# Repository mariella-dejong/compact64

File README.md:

# Compact 64

A smaller form-factor Commodore 64 that is built around the **original MOS
6510 CPU, VIC-II and SID chips**.

The project starts from a faithful KiCad replica of the C64 "250407"
motherboard and evolves it step by step: the original chips stay, while the
rest of the board is either kept as-is or replaced with present-day parts and
modern solutions where that makes the machine smaller, easier to build or more
convenient to use.

> **Status:** work in progress. The schematic is being redesigned step by
> step, starting from the 250407 replica. The PCB layout is not kept in sync
> with these changes and reflects an earlier state of the design: the board
> will be laid out again from scratch for the smaller form factor once the
> schematic is complete. Do not use the current PCB files for manufacturing.
> Nothing here has been built or tested yet in its modified form.

## Goals

- Keep the heart of the C64 genuine: the original 6510, VIC-II and SID chips
  run the show.
- Shrink the board to a smaller form factor.
- Make it buildable today: use parts that can actually be sourced, and put
  chips that can only be salvaged from old machines in sockets.
- Replace parts of the design that are obsolete, hard to source or
  inconvenient with modern equivalents.
- Stay open: publish all design files in their native, editable format.

## Roadmap

The work is tracked in the issue tracker. In broad strokes:

**Phase 1 - Hardware: a clean, modern base design**

- Import the reverse-engineered 250407 design (#1)
- Upgrade the design to KiCad 10 (#2)
- Restructure the hierarchical schematic (#3)
- Make schematic and PCB fully consistent (clean ERC and DRC) (#4)
- Add LCSC part numbers for sourceable components, NTSC variants first (#5)
- Use IC sockets for chips that can no longer be sourced new (#6)
- Replace obsolete passive and other non-chip components (#14, #15)

**Phase 2 - Hardware: modernisation**

- Replace the RF modulator with an on-board composite and S-Video circuit
  (#8), and add S-Video and audio outputs (#24, #9)
- Power the board from a single 12 V DC input (#10) and generate the supply
  rails from it (#26), starting with the 5 V buck converter (#28),
  `CAN+5V` (#34), `+12V` (#36, replaced by `+9V` in #73), the cassette
  motor supply (#41) and `+3V3` (#44), and remove the 9 V AC input (#37)
- Add a supervisor microcontroller that only lets the system power up when
  it is safe to do so (#46)
- Replace RAM and ROM with a microcontroller-based solution (#11)
- Replace CIA1 (#25) and CIA2 (#68) with a microcontroller-based solution
- Replace the keyboard connector with a USB keyboard to keyboard-matrix
  bridge (#12); the USB keyboard port is on the CIA1 controller (#25)
- Move to the chip set of the later C64 boards: the 8580 SID (#73), the 8562
  VIC-II (#74), later the PAL 8565 (#152), and the 8500 CPU (#75)

**Phase 3 - Firmware and software**

- Wireless (Bluetooth or Wi-Fi) media access, for example an emulated disk
  drive fed by a PC application (#13)
- Firmware for the microcontroller-based subsystems above

## Repository layout

| Path                  | Contents                                                        |
| --------------------- | --------------------------------------------------------------- |
| `hardware/main-board` | KiCad project of the main board (starts as the 250407 replica)  |
| `hardware/components` | KiCad symbols and footprints that KiCad's own libraries lack    |
| `hardware/led-module` | KiCad project of the status LED module, cabled to the main board |
| `LICENSES/`           | Full texts of all licences used in this repository              |
| `LICENSE.md`          | Which licence applies to which part of the repository           |
| `NOTICE.md`           | Credits, third-party attributions and trademark notices         |
| `CONTRIBUTING.md`     | How to contribute, and the conventions for issues and pull requests |

Firmware and software will get their own top-level directories once that work
starts.

## Tools

The hardware is designed in [KiCad](https://www.kicad.org/) 10 (#2). The
imported replica was last saved with KiCad 9.0.

## Contributing

Contributions are welcome. See [CONTRIBUTING.md](CONTRIBUTING.md) for how to
get started, the conventions for issues and pull requests, and the licensing
of contributions.

## Credits

This project would not exist without the C64 250407 replica by **Bwack** and
the people who helped create it, most notably **Michael K. (Der Alte
Bastler)**, who started the reverse engineering effort. See
[NOTICE.md](NOTICE.md) for the full list of credits and third-party
attributions.

The composite and S-Video output circuit that replaces the RF modulator is
derived from the C64 RF Modulator Replacement by **mbarszcz-pcb**.

- Upstream project: <https://github.com/bwack/C64-250407-Replica-KiCad>
- RF modulator replacement: <https://github.com/mbarszcz-pcb/c64-rf-modulator-replacement>

## Licence

In short:

- **Hardware** design files (`hardware/`) are licensed under the
  [CERN Open Hardware Licence Version 2 - Strongly Reciprocal](LICENSES/CERN-OHL-S-2.0.txt)
  (CERN-OHL-S-2.0).
- **Firmware and software** will be licensed under the
  [Apache License 2.0](LICENSES/Apache-2.0.txt).
- **Documentation** outside `hardware/` is licensed under
  [Creative Commons Attribution 4.0 International](LICENSES/CC-BY-4.0.txt)
  (CC-BY-4.0).

See [LICENSE.md](LICENSE.md) for the details, including how to attribute this
work when you reuse it.

## Disclaimer

This is an independent hobby project. It is not affiliated with, endorsed by
or sponsored by the owners of the Commodore, Commodore 64 or C64 trademarks,
or by MOS Technology or its successors. See [NOTICE.md](NOTICE.md).

The design files are provided as-is, without any warranty. Building
electronics involves risks, including working with mains-powered equipment
and soldering; you build and use anything from this repository at your own
risk.

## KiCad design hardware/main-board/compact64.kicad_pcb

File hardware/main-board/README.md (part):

# Main board

KiCad project of the Compact 64 main board. Open `compact64.kicad_pro` in KiCad.

The design starts as an unmodified copy of the
[C64 250407 Replica](https://github.com/bwack/C64-250407-Replica-KiCad) by
Bwack: a reverse-engineered replica of the Commodore 64 assembly 250407
motherboard (PCB KU-14194HB). It will be modified step by step into the
Compact 64 main board; see the [project README](../../README.md) for the
roadmap.

## Status

The schematic is under active redesign. The PCB layout is not updated along
with it: it includes the changes up to and including the HF module
replacement (#8), but not the `Power Supply` sheet (#10) or later changes.
Because the board will be laid out again from scratch for the smaller form
factor once the schematic is complete, intermediate schematic changes are
not carried over to the current layout. Expect the DRC schematic parity
check to report these differences, and do not use the current PCB files for
manufacturing.

The board now runs from a single 12 V DC input (#10, #26). All supply rails
are made from it on the `Power Supply` sheet. The original power brick input
is gone (#37): the power connector CN7, the 9 V AC and `+9V_UNREG`, and the
power switch SW1, so the board has no power switch.

The SID is now an 8580 on a 9 V supply (#73), and the VIC-II an HMOS-II part
on 5 V (#74), so the board no longer needs 12 V anywhere and the `+12V` rail
is gone. The VIC-II is the PAL 8565 (#152), because the NTSC 8562 can hardly
be bought any more; an 8562 still works with the NTSC clock setting.

The VIC-II's colour and dot clocks now come from a clock synthesizer on the
`System Clocks` sheet (#76). It replaces the PLL of the original board, whose
MC4044 can no longer be bought, and the colour clock divider that
synchronized the buck converters.

What is left of the original 250407 circuit, the 6510 with the cassette
port and the expansion port, is now on one flat sheet, `CPU, Cassette and Expansion Port` (#84, #107), with SMD passives and
reference numbers in the 200 range, see
[CPU, cassette and expansion port](#cpu-cassette-and-expansion-port). Its
power-on reset timer is gone: the supervisor now resets the system at
start-up (#89), see [Soft reset](#soft-reset).

The PLA (U17), the 74LS139 (U15), the 7408 (U27) and the `~AEC` inverter of
the original board are replaced by a CPLD on the `PLA Replacement` sheet
(#83), see [PLA replacement](#pla-replacement).

The supervisor has a micro SD card slot (#95), from which it will load disk
and tape images (#13), see [SD card slot](#sd-card-slot).

The status LEDs (power, ready, activity, error) sit on a separate LED module
that connects to the supervisor with a short cable, so that they can be
mounted in the case (#54), see [Status LEDs](#status-leds). The original
power LED connector is gone.

## Compatibility

These changes make the Compact 64 behave differently from an original C64.
Check them before using software or hardware that depends on them.

### CIA time-of-day clocks run from a crystal

- **Original C64:** both CIAs (U1 and U2) get a 50 Hz or 60 Hz signal on
  their TOD input (pin 19). It is derived from the 9 V AC of the power brick
  and buffered by gate A of U27, so the clocks follow the mains frequency.
- **Compact 64:** there is no 9 V AC (#37). Both CIAs are replaced by
  microcontrollers (#25, #68) that make the 50 Hz or 60 Hz reference from
  their own crystal, as selected by bit 7 of CRA (see
  [CIA 1, keyboard and joysticks](#cia-1-keyboard-and-joysticks) and
  [CIA 2, serial port and user port](#cia-2-serial-port-and-user-port)).
  U27 is gone as well (#83).
- **Not affected:** software that uses the time-of-day clocks, the TOD
  alarms or the CIA timers, provided the firmware implements them.
- **Affected:** only software that expects the TOD clocks to follow the
  mains frequency exactly. The crystal reference is more stable than the
  mains, so a TOD clock can drift a little differently from an original C64.

### User port pins 10 and 11 carry no 9 V AC

- **Original C64:** pins 10 and 11 of the user port (CN2) carry the 9 V AC of
  the power brick, one side through fuse F1.
- **Compact 64:** both pins are unconnected, and not grounded (#37). The user
  port is now J1602 on the `CIA2, Serial Port and User Port` sheet (#68).
- **Affected:** devices that take their power from these pins, such as some
  RS-232 interfaces and EPROM programmers. They need their own supply.
  Devices that only use the +5 V on pin 2 and the data lines are not
  affected.

### No 8-pin DIN A/V connector

- **Original C64:** the A/V connector (CN5) is an 8-pin DIN socket with luma
  (pin 1), ground (pin 2), audio out (pin 3), composite video (pin 4), audio
  in (pin 5) and chroma (pin 6).
- **Compact 64:** CN5 is removed (#24). The same signals are on a 4-pin
  mini-DIN S-Video socket (J501) and three RCA jacks (J502), see
  [Audio and video connectors](#audio-and-video-connectors).
- **Affected:** C64 A/V cables with a DIN plug, such as DIN to RCA, DIN to
  S-Video and DIN to SCART cables. Use standard S-Video and RCA cables
  instead.

### RAM and ROM are served by a microcontroller

- **Original C64:** eight 4164 DRAMs, the BASIC, KERNAL and character ROMs,
  and a 2114 colour RAM.
- **Compact 64:** a microcontroller (U1401) serves all of them from its own
  memory (#11), see [RAM and ROM replacement](#ram-and-rom-replacement). It
  loads the ROM images from an EEPROM. The ROM images are not part of this
  project.
- **Affected:**
  - The board does not start without the controller's firmware and ROM
    images.
  - ROM upgrades that replace a chip, such as a replacement KERNAL chip,
    cannot be fitted. Write a different image to the EEPROM instead.
  - The RAM contents at power-up are set by the firmware, not by the DRAMs'
    power-up pattern. The same goes for other details of DRAM behaviour,
    such as what ends up in RAM when the 6510 writes to $00 or $01.
- **Not affected:** bank switching, cartridges and the VIC-II bank
  selection. The CPLD that replaces the PLA (U301) decodes them as before.

### CIA 1 is emulated by a microcontroller, and the keyboard is USB

- **Original C64:** a 6526 CIA (U1) at $DC00 scans the keyboard matrix on
  connector CN1 and reads the two control ports (CN8, CN9).
- **Compact 64:** a microcontroller (U1501) takes the place of CIA 1 (#25),
  see [CIA 1, keyboard and joysticks](#cia-1-keyboard-and-joysticks). The
  keyboard is a USB keyboard on a USB-A socket (J1501), and the firmware
  presents it to the 6510 as the C64 keyboard matrix. RESTORE is a key on
  the USB keyboard chosen by the firmware. The control ports are new DE-9
  sockets (J1502, J1503) with the original pinout.
- **Affected:**
  - The board does not start without the controller's firmware.
  - An original C64 keyboard, or anything else made for the 20-pin keyboard
    connector, cannot be connected.
  - How closely the 6526 is matched (timers, interrupts, the serial shift
    register, keyboard ghosting) depends on the firmware. Programs that rely
    on exact CIA timing or on unusual keyboard matrix tricks need firmware
    that reproduces them.
  - The digital control port lines now have 10k pull-ups to +5V and a
    100 Ohm series resistor, instead of the 6526's internal pull-ups. The
    levels stay the same: a line idles at 5 V and a pressed switch pulls it
    to about 0.05 V.
- **Not affected:** paddles and the POT lines (the 4066 that switches them,
  now U1702, works as before), the light
  pen input of the VIC-II, cassette read and the serial bus SRQ on `~FLAG`,
  and `CNT` and `SP` on the user port.

### CIA 2 is emulated by a microcontroller

- **Original C64:** a 6526 CIA (U2) at $DD00 selects the VIC-II bank, drives
  and reads the serial bus through U8 (7406), and serves the user port
  (CN2).
- **Compact 64:** a microcontroller (U1601) takes the place of CIA 2 (#68), see
  [CIA 2, serial port and user port](#cia-2-serial-port-and-user-port). The
  serial port (J1601) and the user port (J1602) keep their original pinout.
- **Affected:**
  - The board does not start without the controller's firmware.
  - How closely the 6526 is matched (timers, NMI timing, the serial shift
    register, `~PC` and `~FLAG`) depends on the firmware. Fast loaders,
    RS-232 on the user port and demos that switch the VIC-II bank at exact
    cycles need firmware that reproduces the 6526 cycle by cycle.
  - The serial bus driver U1602 (SN74LVC06A) sinks up to 24 mA, the original
    7406 up to 40 mA. Every device on the bus adds its own pull-up of about
    1k (5 mA). The C64 and three such devices stay within the rating; more
    devices with 1k pull-ups may pull the low level up too far.
  - The user port lines have 4.7k pull-ups to +5V, a 100 Ohm series
    resistor and a TVS diode instead of the 6526's internal pull-ups. A line
    still idles at 5 V. An output that is set high is released to the
    pull-up instead of being driven, so its rising edge is a little slower
    (about 0.5 us with 100 pF of cable).
- **Not affected:** the VIC-II bank selection after reset (bank 0, also
  before the firmware runs), the serial bus pinout, the user port pinout
  except pins 10 and 11 (see above), and `CNT` and `SP` of CIA 1 on the user
  port.

### The CPU is an 8500

- **Original C64:** the 250407 board has an NMOS 6510 CPU (U7).
- **Compact 64:** the CPU socket (U201) takes the HMOS-II 8500 of the later
  C64C boards (#75), see
  [CPU, cassette and expansion port](#cpu-cassette-and-expansion-port). The
  8500 is the 6510 made in the newer process: same pinout, same 5 V supply,
  same bus timing and the same processor port, so the circuit is the same
  for both. It also runs cooler. A 6510 works in the socket as well. This
  README calls the CPU the 6510 when it describes its pins and bus cycles.
- **Affected:**
  - The unused bits 6 and 7 of the processor port ($01) keep a written value
    for a while after the port is switched to input, until the charge leaks
    away. This takes noticeably longer on an 8500 than on a 6510 (VICE
    assumes about 1.5 s against about 0.35 s), and on both chips it depends
    strongly on the chip and the temperature. A few copy protections and
    test programs measure it.
  - The unstable undocumented opcodes (such as ANE/XAA and LXA) use a
    "magic constant" that differs between chips, including between 6510 and
    8500 chips, and with temperature. Programs that rely on them may behave
    differently, as they also do between two original C64s.
  - Original 8500 and 6510 chips are only available second-hand.
- **Not affected:** the documented instruction set, the bus and interrupt
  timing, the processor port bits 0 to 5 (memory configuration and the
  cassette lines) and their pull-ups.
- **Not the 8502:** the 8502 is the C128's CPU and is not a drop-in
  replacement.

### The SID is an 8580

- **Original C64:** the 250407 board has a 6581 SID (U18) with 12 V on VDD
  and 470 pF filter capacitors.
- **Compact 64:** the SID socket (U1701) takes the 8580 of the later C64
  boards, with 9 V on VDD and 22 nF filter capacitors (#73), see
  [SID and audio output](#sid-and-audio-output).
- **Affected:**
  - Music sounds different. The 8580's filter is cleaner and more linear,
    it has less background noise and its combined waveforms differ. Music
    written for the 6581, which is most classic SID music, can sound
    noticeably different, especially where it uses the filter.
  - Samples played by writing the volume register ($D418) are almost silent
    on an 8580. A resistor from EXT IN to ground can bring them back; the
    board does not have one.
  - A 6581 must not be fitted: it would get 9 V instead of 12 V on VDD and
    the wrong filter capacitors.
- **Not affected:** the SID's registers, the paddles and the audio
  connectors. Modern SID replacements usually accept 9 V on VDD; check the
  specific product.

### The VIC-II is a PAL 8565

- **Original C64:** the 250407 board has an NMOS 6567 VIC-II (U19, NTSC) with
  12 V on VDD (pin 13) and a 470 Ohm luma pull-up; PAL boards have the 6569.
- **Compact 64:** the VIC-II socket (U504) takes the HMOS-II 8565 of the later
  PAL C64 boards (#152), with 5 V on pin 13 and a 1 kOhm luma pull-up (#74),
  see [VIC-II](#vic-ii). The NTSC 8562 has the same pinout and supply and
  also works, with the NTSC clock setting in the supervisor firmware; the
  board was built around it first, but it can hardly be bought any more.
- **Affected:**
  - The video timing is PAL: 63 cycles per line and 312 lines (50 Hz), with
    the CPU at 0.985 MHz, the same as a PAL C64 with a 6569 or 8565.
    Software written for PAL machines runs as on a PAL C64; NTSC-only
    software that depends on 65 cycles and 263 lines may not.
  - The SID runs from the PAL `PHI2`, so music plays at the pitch of a PAL
    C64.
  - Colours and luma levels differ slightly from the NMOS 6567 and 6569.
  - The 8565 shows "grey dots" when some colour registers are written at
    certain cycles, which a few demos trigger.
  - A 6567 or 6569 does not work in this socket: they need 12 V on pin 13.
- **Not affected:** the registers, sprites, raster interrupts and the light
  pen.

### The video clocks come from a clock synthesizer

- **Original C64:** a PLL on the 250407 board (Y1, U29 to U32) makes the
  colour clock from a 14.31818 MHz crystal and locks the dot clock to it.
  PAL or NTSC is set with the crystal, some component values and a jumper.
- **Compact 64:** an MS5351M clock synthesizer (Y1202) makes both clocks from
  one PLL and a 25 MHz crystal (#76), see [System clocks](#system-clocks).
  The supervisor programs it over I2C, so PAL or NTSC becomes a firmware
  setting. PAL is the default, for the 8565 (#152); NTSC is only for a board
  with an 8562. The setting must match the fitted VIC-II.
- **Affected:**
  - Without supervisor firmware the VIC-II gets no clocks. The board already
    needs firmware for RAM, ROM and both CIAs.
- **Not affected:** the video timing and the ratio between the dot clock
  and the colour clock (4/9 on PAL, 4/7 on NTSC), which the synthesizer makes
  exactly. The colour
  carrier is as accurate as the 25 MHz crystal (10 ppm).

### The PLA is a CPLD

- **Original C64:** a 906114-01 PLA (U17) decodes the memory map, a 74LS139
  (U15) the I/O area, and a 7408 (U27) and a 7406 gate (U8) make `RDY`,
  `CAEC`, `~COLORAM` and `~AEC`.
- **Compact 64:** one XC9572XL CPLD (U301) does all of this (#83), with logic
  written from the PLA's documented equations (#93), see
  [PLA replacement](#pla-replacement). The supervisor checks its design at
  start-up and programs it when needed (#86).
- **Affected:**
  - The board does not start without the supervisor firmware, which also
    enables the CPLD's outputs.
  - The chip selects come out about 10 ns after the inputs change, earlier
    than from the PLA and the 74LS139. Cartridges that are sensitive to PLA
    timing need testing on the prototype.
  - The chip selects on the expansion port (`~ROML`, `~ROMH`, `~I/O1`,
    `~I/O2`) are 3.3 V signals, at TTL levels like the original ones.
- **Not affected:** the memory map, bank switching through $01, the
  cartridge modes set by `~GAME` and `~EXROM` (including Ultimax), the I/O
  map and DMA through `~DMA`, provided the logic matches the PLA (#93).

## Power supply

The board is being converted to a single 12 V DC input (#10, #26). The rails
made from it so far are on the `Power Supply` sheet:

| Rail       | Made by                                                     | Rated for | Issue |
| ---------- | ----------------------------------------------------------- | --------- | ----- |
| `12V_PROT` | Input stage: barrel jack, polyfuse, reverse polarity and TVS protection | 2.5 A (polyfuse hold current) | #10   |
| `12V_MAIN` | Power switch (Q606, Q607), set by the power switch on the case; feeds `+3V3` and the input switch | 2.5 A | #109 |
| `12V_IN_SW` | Input switch (Q604, Q605), turned on by the supervisor; feeds every rail below except `+3V3` | 2.5 A | #47   |
| `+5V`      | LM61440 synchronous buck converter (U701), synchronized to the clock synthesizer | 2 A       | #28   |
| `CAN+5V`   | L78M05 linear regulator (U801) behind four M7 diodes        | 500 mA    | #34   |
| `+9V`      | CJ78M09 linear regulator (U902) from the switched 12 V input | 500 mA (regulator) | #36, #73 |
| `CASS_POWER` | TPS562208 synchronous buck converter (U1101), switched on and off by the 6510 | 2 A       | #41   |
| `+3V3`     | LM61440 synchronous buck converter (U1001), synchronized to the clock synthesizer; backed up from `+5V` by U1002 (#110) | 1 A budget (converter rated 4 A) | #44, #110 |

The HF module replacement (U501, a 78L05 behind R501) also runs from the
switched 12 V input: the `Power Supply` sheet passes `12V_IN_SW` on through a
sheet pin of the same name to the `VIC-II, HF Module Replacement and AV out`
sheet. The `5V Buck` sheet's output reaches the root sheet through the `5V_OUT` sheet
pin, where it connects to the `+5V` power symbol.

The `System Clocks` sheet supplies the sync clock for the switching parts,
see [System clocks](#system-clocks). U1201 (74AHCT1G08) passes output CLK2
of the clock synthesizer, about 445 kHz, only once `PGOOD` is high. It
reaches the 5 V and 3.3 V buck converters through the `SYNC_CLK_IN` sheet pin
of the `Power Supply` sheet. CLK2 comes from the same PLL as the colour and
dot clocks, so the converters' interference has a fixed relation to the
video timing. U1201 runs from `CAN+5V`.

`PGOOD` combines the open-drain PGOOD outputs of both buck converters (U701
and U1001) with the pull-ups R706 and R1003 (200k each) on `CAN+5V`: a
wired-AND. It leaves the `Power Supply` sheet through the `PGOOD` sheet pin.
It goes high once both outputs are in regulation, after the 1.5 ms to 2.5 ms
PGOOD delay. The supervisor reads it on GPIO3 through R1330 (#49), see [Chip
and rail checks](#chip-and-rail-checks). If either rail drops out of
regulation, the sync clock stops and both converters run unsynchronized at
about 400 kHz, set by R701 and R1002, until `PGOOD` returns.

### 12 V path

The 12 V input passes three stages, and each stage has its own net name:

```
J601 ── F601 ── Q601/Q602 ── 12V_PROT ── Q606/Q607 ── 12V_MAIN ── Q604/Q605 ── 12V_IN_SW
 jack   fuse    reverse         TVS D602   power switch   U1001 (+3V3)  input switch  all other rails
                polarity        C605       (case switch)                (supervisor)
```

| Net | Connected |
| --- | --------- |
| `12V_PROT` | After the reverse polarity protection: TVS D602, C605 (220 nF), the zener D601 of Q601/Q602, the power switch Q606/Q607 with R606 and C604 |
| `12V_MAIN` | After the power switch: C601, C602, 3V3 buck converter U1001 with its input capacitors and EN pull-up R1001, the input switch Q604/Q605 with R605 and C603 |
| `12V_IN_SW` | After the input switch: 5V buck converter U701 with R705, cassette buck converter U1101 with R1103, `CAN+5V` (D801 to U801), `+9V` (FB901 to U902), HF module replacement (R501) |

The converter sheets call their input `VIN`. That hierarchical label always
means "the input of this converter" and connects to `12V_MAIN` or
`12V_IN_SW` on the `Power Supply` sheet.

### Power switch

The power switch (#109) turns the whole board on and off, including
`+3V3` and the supervisor. A small switch in the case (on J602) steers a
P-channel MOSFET pair, so the switch itself only carries microamps.

```
12V_PROT ──┬───────────── Q606/Q607 (2x AO3401A, source on 12V_PROT) ── 12V_MAIN
           │                   │ gate (PWR_SW_GATE)
           ├── R606 100k ──────┤
           └── C604 47 nF ─────┤
                               └── R607 100k ── J602 pin 2 ── case switch ── J602 pin 1 ── GND
```

- **Off (switch open):** R606 holds the gate at the source, so Q606 and
  Q607 are off. They are mounted the other way round from Q601/Q602
  (source on the input side), so their body diodes block, and the board
  draws nothing.
- **On (switch closed):** R606 and R607 divide the gate to about half the
  input voltage: about -6 V gate-source at 12 V, and about -10.75 V at the
  21.5 V clamping voltage of D602, within the AO3401A's +/-12 V limit. Two
  in parallel carry the full 2.5 A at about 0.17 W, like the input switch.
- **Why a second pair:** Q601/Q602 (reverse polarity protection) cannot be
  reused. Their body diodes conduct in the normal direction, so the board
  would keep running through them while they are off.
- **C604 (47 nF):** slows the switch-on (time constant about 2.4 ms), so
  that C601, C602 and the converters' input capacitors charge gently, and
  keeps the gate at the source when the adapter is plugged in with the
  switch off.
- **ESD:** the switch sits in the case on a cable. R607 is on the gate side
  of J602, so a discharge into the cable reaches the gate only through
  100k, where C604 absorbs it. D602 and C605 sit before the switch, so the
  input stays protected while it is off.
- **Power-off order:** switching off looks exactly like unplugging the
  adapter. `+3V3` is backed up from `+5V` (#110), so it never drops while
  `+5V` is still up, see [Backup from `+5V`](#backup-from-5v-110).
- **Consequences:** with the switch off, the supervisor is off too, so the
  SD card cannot be reached over USB, and a firmware update cannot delay
  the switch-off; the firmware tolerates a sudden power loss (#111).
- **Reverse polarity:** Q601/Q602 still block a reversed input, and Q606
  and Q607 stay off.

| Ref | Part | LCSC | Package |
| --- | ---- | ---- | ------- |
| Q606, Q607 | AO3401A | C15127 | SOT-23 |
| R606, R607 | 100k | C25741 | 0402 |
| C604 | 47 nF | C1622 | 0603 |
| C605 | 220 nF | C21120 | 0603 |
| J602 | 1x2 pin header, 2.54 mm, for the case switch | C32713268 | THT |

The case switch itself is not on the board. Any small latching switch
works, for example a KCD11 mini rocker switch that snaps into a 10 x 15 mm
cut-out.

### Input switch

The supervisor (U1301) decides when the system may start (#47). It does this
with one switch in the 12 V input: every rail except `+3V3` runs from the
switched input `12V_IN_SW`, so a single signal turns them all on or off.
`+3V3` stays on `12V_MAIN`, before the input switch, because it powers the
supervisor.

**Circuit:**

- Q604 and Q605 (AO3401A, P-channel) in parallel, sources on `12V_MAIN`,
  drains on `12V_IN_SW`. Two in parallel halve the on-resistance to about
  28 mOhm, so they dissipate about 0.17 W at 2.5 A.
- R605 (100k) pulls their gates to the source, so they are off by default.
- Q603 (AO3400A, N-channel) pulls the gates down through R604 (100k). R604
  and R605 form a divider, so the gates go to about half the input voltage
  instead of to ground: about -6 V gate-source at 12 V, and about -10.75 V
  at the 21.5 V clamping voltage of D602, within the AO3401A's +/-12 V
  limit.
- Q603's gate is driven by `POWER_ON` through R602 (10k), with R603 (200k)
  to ground.
- C603 (47 nF) between the gates and `12V_MAIN` does two things. It keeps
  the gates at the source voltage when the adapter is plugged in, so the
  MOSFETs' gate-drain capacitance cannot turn them on briefly. And it slows
  down switching: the gates move with a time constant of about 2.4 ms when
  turning on and about 4.8 ms when turning off, which limits the inrush
  current into the input capacitors of the rails to well under 1 A.
- A PWR_FLAG on `12V_IN_SW` tells ERC that the MOSFETs drive this net.

**Operation** (12 V input):

| State | `POWER_ON` | Q603 gate | Q604/Q605 gate | Q604/Q605 gate-source | `12V_IN_SW` |
| ----- | ---------- | --------- | -------------- | --------------------- | ----------- |
| Off   | 0 V or not driven | 0 V | 12 V | 0 V | off |
| On    | 3.3 V      | 3.14 V    | 6 V            | -6 V                  | about 12 V  |

Q603 is fully on at 3.14 V (threshold at most 1.45 V); Q604 and Q605 are
fully on at -6 V (threshold at most -1.3 V). Q603 draws 60 uA through R604
and R605, and `POWER_ON` supplies 16 uA.

**Fail-safe default:** the rails stay off unless the supervisor's firmware
drives `POWER_ON` high.

- **Supervisor unpowered:** R603 holds Q603's gate at ground.
- **Supervisor in reset or booting:** RP2350 GPIOs come out of reset with
  the output disabled and the internal pull-down on. The boot ROM does not
  use GPIO2, whether it boots from flash or starts the USB bootloader.
- **Blank firmware:** the USB bootloader leaves GPIO2 alone, so the rails
  stay off. A board without supervisor firmware does not start.
- **Reset while running:** pressing RESET or a watchdog reset returns GPIO2
  to its reset state, which turns the rails off.

**Back-feeding:** while `12V_IN_SW` is off, only `+3V3`, the supervisor and
the RAM and ROM controller (U1401 to U1403) are powered.

- `PGOOD` is pulled up to `CAN+5V`, which is off, so it does not feed the
  unpowered gate U1201 on the `System Clocks` sheet.
- The sync clock reaches U1001's EN/SYNC through C1005, which blocks the DC
  on that pin from the unpowered gate U1201.
- The clock synthesizer (Y1202) runs from `+3V3` and stays powered. Its
  outputs stay disabled (low) until the supervisor enables them, and the
  74AHCT inputs of U1201 to U1203 tolerate 3.3 V while `CAN+5V` is off, see
  [System clocks](#system-clocks).
- U902 runs from `12V_IN_SW`, so `+9V` stays off as well.
- The supervisor's only connection to the legacy chips is `~RESET` (#70).
  Q1301 can only pull it low, and GPIO1 reads it through R1315, so neither
  feeds the unpowered chips, see [Soft reset](#soft-reset). Later issues that add more
  connections must keep them from feeding unpowered chips as well.
- The RAM and ROM controller connects to the C64 buses. It keeps all its bus
  pins as inputs while the rails are off, see
  [Power and back-feeding](#power-and-back-feeding).

**Side effects:**

- With the rails off, `PGOOD` is low and `+3V3` runs unsynchronized at about
  400 kHz. It locks to the sync clock once the other rails are up and the
  supervisor has enabled the synthesizer's outputs.
- The cassette motor supply U1101 is on the switched input, so it stays off
  until the supervisor starts the system. After that the 6510 controls it
  through P5, as before.
- All rails start together; there is no start-up order between them.

### `CAN+5V` current budget

`CAN+5V` powers the VIC-II (VCC and, since #74, VDD) and the three 5 V
gates on the `System Clocks` sheet (#76): the clock buffers U1202 and U1203
and the sync gate U1201.

| Load                                        | Typical             | Maximum  | Source                                                    |
| ------------------------------------------- | ------------------- | -------- | --------------------------------------------------------- |
| VIC-II 8565 (U504), VCC (pin 40)            | not specified       | 200 mA   | 6567 figure (preliminary datasheet, 3.3.7: ICC, outputs open), used as an upper bound |
| VIC-II 8565 (U504), VDD (pin 13)            | not specified       | 50 mA    | 6567 figure (3.3.7: IDD), used as an upper bound          |
| 74AHCT1G125 (U1202), colour clock           | about 2 mA          | about 3 mA | Cpd 14 pF plus about 15 pF load at 14.3 MHz, plus the change in supply current (1.35 mA with a 3.4 V input) for the half of the time the input is high (TI SN74AHCT1G125) |
| 74AHCT1G125 (U1203), dot clock              | about 2.6 mA        | about 3.5 mA | Cpd 14 pF plus about 50 pF load (C518, the VIC-II and the expansion port) at 8.2 MHz, plus the same change in supply current |
| 74AHCT1G08 (U1201), sync clock              | about 4.5 mA        | about 5.3 mA | Charging C710 and C1005 (1 nF each) at about 445 kHz, plus the same change in supply current (TI SN74AHCT1G08) |
| R706 and R1003 (PGOOD pull-ups)             | 0.05 mA             | 0.05 mA  | 5 V / 100 kOhm (two 200k in parallel)                     |
| R1331 and R1332 (rail check divider, #49)   | 0.34 mA             | 0.34 mA  | 5 V / 14.7 kOhm                                           |
| **Total**                                   | **about 9 mA plus the VIC-II** | **about 262 mA** |                                       |

No 8565 or 8562 datasheet figures were found, so the 6567's maximum currents
are used as an upper bound; the HMOS-II 856x draws considerably less in
practice.
Measure the real `CAN+5V` current on the first prototype.

Datasheets:
[6567 VIC-II preliminary](https://archive.org/details/mos_6567_vic_ii_preliminary),
[SN74AHCT1G125](https://www.ti.com/lit/ds/symlink/sn74ahct1g125.pdf),
[SN74AHCT1G08](https://www.ti.com/lit/ds/symlink/sn74ahct1g08.pdf),
[L78M](https://www.st.com/resource/en/datasheet/l78m.pdf).

With this budget, the L78M05 (500 mA) runs at up to about 52 % of its rating.
The four M7 diodes in front of it drop about 3.2 V to 3.6 V and take part of
the heat:

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
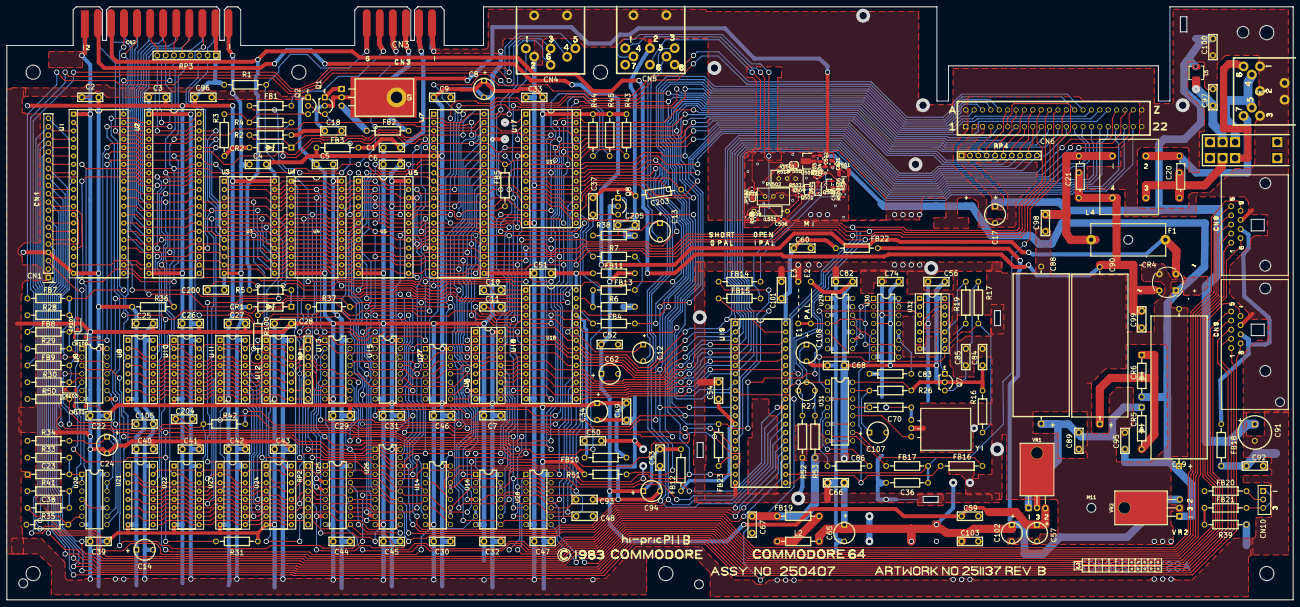
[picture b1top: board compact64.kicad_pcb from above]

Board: 2 copper layers, 390.0 x 179.8 mm, 253 parts (0 on the bottom side), 235 nets.

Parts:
C1, C2, C3, C4, C5, C6, C7, C9, C18, C22, C25, C26, C27, C28, C29, C30, C31, C32, C33, C39, C40, C41, C42, C43, C44, C45, C46, C47, C49, C50, C51, C52, C53, C54, C56, C59, C60, C66, C67, C68, C74, C82, C84, C89, C92, C95, C96, C98, C99, C101, C103, C105, C200: .1; CAP_P5.08mm
C8, C12, C13, C14, C17, C24, C34, C57, C62, C65, C94, C102, C107, C108: 10uF; CAP_ELYT_RADIAL_P5.08mm_SMALL_RING
C10, C11: 470pF; CAP_P5.08mm
C19: 2200uF; LARGE_ELECTROLYTIC_AXIAL_TH
C20, C21: .22; CAP_POLY_100V_TH_P5.08_and_P12.07mm
C23: 360pF; CAP_AXIAL_P12.7mm
C36: 20pF; RESISTOR
C37: 1000pF; CAP_P5.08mm
C38: 51pF; CAP_AXIAL_P12.7mm
C48, C93: 1800pF; CAP_P5.08mm
C70: 16pF 5%; RESISTOR
C83, C86: 82pF; RESISTOR
C85: .47; CAP_P5.08mm
C88: 1000uF; LARGE_ELECTROLYTIC_AXIAL_TH
C90: 470uF; LARGE_ELECTROLYTIC_AXIAL_TH
C91: 100uF; CAP_ELYT_RADIAL_P5.08mm
C97, C100: .22; CAP_P5.08mm
C203: 82pF; CAPACITOR_RADIAL_P13.97_L9.9_D3.6
C204: NC; CAP_P5.08mm
C205: 220pF; CAP_P5.08mm
C501, C504: 10uF; C_0805_2012Metric
C502: 470nF; C_0805_2012Metric
C503: 0.1uF; C_0603_1608Metric
C505: 330pF; C_0603_1608Metric
C506: 68pF; C_0603_1608Metric
CN1: KEYBOARD_20PIN_MALE; PinHeader_1x20_P2.54mm_Vertical
CN2: USER_PORT_CON; EDGE_CON_24P
CN3: CASSETTE_PORT_CON; EDGE_CON_12P_TAPE
CN4: SERIAL_BUS_CON; SERIAL_CON_DIN6
CN5: AV_CONN; AV_CON_DIN8
CN6: EXPANSION_PORT
CN7: POWER_CON; POWER_CON_D7_250407
CN8, CN9: CONTROL_PORT; JOYPORT_DB9
CN10: LED_CONNECTOR; LED_CON
CR1: IN4371; ZENER_12.7mm
CR2: IN755; ZENER_12.7mm
CR4: BRIDGE_RECTIFIER; Diode_Bridge_Round_D9.0mm
CR5, CR6: 1N4001; RECTIFIER_TH_P12.7mm
CR100, CR101, CR102, CR103: 1N4148W; D_SOD-123
D501: 1N4148W; D_SOD-123
E2: JUMPER_WIRE
E3: JUMPER_WIRE_DASHED; JUMPER_WIRE
F1: 1A; Fuseholder_Cylinder-5x20mm_Schurter_0031_8201_Horizontal_Op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
FB1, FB2, FB3, FB4, FB5, FB7, FB8, FB9, FB10, FB11, FB12, FB13, FB14, FB15, FB16, FB17, FB18, FB19, FB20, FB21, FB22, FB23: FERRITE_BEAD; FERRITE_BEAD_TH_P12.7mm
H1, H2, H3, H4, H5, H6, H7: MountingHole; MountingHole_4.3mm_M4
H8: MountingHole; MountingHole_3.5mm
H9, H10, H11, H12: MountingHole; MountingHole_2.7mm_M2.5_ISO7380
JP502: RV2 Bypass; SolderJumper-2_P1.3mm_Open_RoundedPad1.0x1.5mm
JP503: RV1 Bypass; SolderJumper-2_P1.3mm_Open_RoundedPad1.0x1.5mm
L2: 2.2uH; RESISTOR
L4: CHOKE
L5: 1.2uH; L_Changjiang_FXL0420
L501: 10uH; L_Axial_L6.6mm_D2.7mm_P10.16mm_Horizontal_Vishay_IM-2
Q1, Q2, Q7, Q8: 2SC1815; Q_NPN_ECB
Q3: TP29B/2SD880; TO-220-3_Horizontal_TabDown_250407
Q501, Q502: BC847; SOT-23
R1, R43, R44, R45: 3K3; RESISTOR
R2, R51: 1.5K; RESISTOR
R3, R7: 10K; RESISTOR
R4, R6, R16, R28, R29, R30, R31, R36, R38, R100: 1K; RESISTOR
R5: 560; RESISTOR
R17, R37: 2K7; RESISTOR
R19: 15K; RESISTOR
R26: 100; RESISTOR
R27: 500; POTMETER
R33, R34: 47K; RESISTOR
R35: 470K; RESISTOR
R39: 390; RESISTOR
R41, R50: 1M; RESISTOR
R42: 82; RESISTOR
R52: 680; RESISTOR
R53: 910; RESISTOR
R501: 47; R_1210_3225Metric
R503: 1K; R_0603_1608Metric
R504: 3.3K; R_0603_1608Metric
R505: 5.6K; R_0603_1608Metric
R506, R508, R510: 150; R_0603_1608Metric
R507: 75; R_0603_1608Metric
R509: 68; R_0603_1608Metric
R511: 220; R_0603_1608Metric
R512: 470; R_0603_1608Metric
RP1, RP2: 33R isolated; RP_ARRAY_7WAY
RP3: 3K3 Bussed; RP_ARRAY_7WAY
RP4: 3K3 Bussed; RP_ARRAY_9WAY
RV501: 220; Potentiometer_Bourns_3296W_Vertical
RV502: 1K; Potentiometer_Bourns_3296W_Vertical
SW1: POWER_SWITCH
U1: CIA_U1; DIP-40_W15.24mm_Socket
U2: CIA_U2; DIP-40_W15.24mm_Socket
U3, U4: 2364A; DIP-24_W15.24mm_Socket
U5: 2332A; DIP-24_W15.24mm_Socket
U6: 2114; DIP-18_W7.62mm_Socket
U7: 6510_MPU; DIP-40_W15.24mm_Socket
U8: 7406N; DIP14
U9, U10, U11, U12, U21, U22, U23, U24: 4164-2; DIP-16_W7.62mm_Socket
U13, U25: 74LS257; DIP16
U14: 74LS258; DIP16
U15: 74LS139; DIP16
U16, U28: 4066_U28; DIP14
U17: PLA_U17; DIP-28_W15.24mm_Socket
U18: 6581; DIP-28_W15.24mm_Socket
U19: VIC; DIP-40_W15.24mm_Socket
U20: 556; DIP14
U26: 74LS373; DIP20
U27: 7408_U27; DIP14
U29: 74LS74; DIP14
U30: 74LS193; DIP16
U31: 74LS629N; DIP16
U32: MC4044; DIP-14_W7.62mm_Socket
U501: 78L05G; SOT-89-3
VR1: 7812; VREG_TO-220-3_Horizontal_TabDown
VR2: 7805; VREG_TO-220-3_Horizontal_TabDown
Y1: Crystal; CRYSTAL

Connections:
+5V: C2.1, C3.2, C4.2, C5.2, C6.2, C7.1, C8.1, C9.1, C14.1, C17.1, C22.1, C25.1, C26.1, C27.1, C28.1, C29.2, C30.1, C31.2, C32.2, C33.1, C34.1, C39.2, C40.1, C41.1, C42.1, C43.1, C44.2, C45.1, C46.1, C47.1, C49.1, C91.1, C92.1, C96.2, C100.2, CN1.4, CN2.2, CN6.2, CN6.3, CR100.1 (K), CR102.1 (K), FB3.2, FB10.2, FB18.1, L5.1, R1.1, R28.2, R29.2, R30.2, R31.2, R33.1, R34.1, R35.1, R36.1, R39.1, R41.1, R43.1, R44.1, R45.1, R50.1, R51.2, RP3.1, RP4.1, U1.20 (VCC), U2.20 (VCC), U3.24 (VCC), U4.24 (VCC), U5.21 (CS2), U5.24 (VCC), U6.18 (VCC), U7.6 (VCC), U8.14, U9.8 (VCC), U10.8 (VCC), U11.8 (VCC), U12.8 (VCC), U13.16, U14.16, U15.16, U16.14 (VDD), U17.28 (VDD), U20.4 (RSTB), U20.10 (RSTB), U20.14 (VCC), U21.8 (VCC), U22.8 (VCC), U23.8 (VCC), U24.8 (VCC), U25.16, U26.20, U27.1, U27.14, U28.14 (VDD)
+9V_UNREG: C18.1, C19.1, C95.1, CR4.1, CR6.2 (A), Q1.2 (C), Q3.2 (C), R2.1, R501.2, VR2.1
+12V: C52.1, C53.1, C57.1, C59.1, C62.1, C94.1, FB11.2, FB12.2, Q8.2 (C), VR1.2
/250407 Design/250407 Sheet 1/5V_FB3: C1.1, CN3.B,2, FB3.1
/250407 Design/250407 Sheet 1/5V_joyport: CN8.7, CN9.7, FB18.2
/250407 Design/250407 Sheet 1/9VAC: C20.2, L4.3, SW1.1
/250407 Design/250407 Sheet 1/9VAC~: C21.2, C90.2, C99.2, CN2.10, CR4.4, L4.4, R5.1
/250407 Design/250407 Sheet 1/60Hz: R37.2, U1.19 (TOD), U2.19 (TOD), U27.3
/250407 Design/250407 Sheet 1/'9VAC~: CN2.11, CR4.2, F1.1
/250407 Design/250407 Sheet 1/+Vc: C56.1, C67.1, C68.1, C74.1, C82.1, C84.1, E2.1, FB19.2, Q7.2 (C), R16.1, R26.1, R53.1, U29.10, U29.13, U29.14, U30.4 (CNT_DN), U30.15 (A), U30.16 (VCC), U31.16 (VCC), U32.14
/250407 Design/250407 Sheet 1/ATN: CN4.3, FB7.1
/250407 Design/250407 Sheet 1/ATN': CN2.9, FB7.2, R28.1, U8.12
/250407 Design/250407 Sheet 1/ATN_OUT: U2.5 (PA3), U8.13
/250407 Design/250407 Sheet 1/BTNB: CN1.16, CN8.6, U1.6 (PA4)
/250407 Design/250407 Sheet 1/CASS_MOTOR: R4.2, U7.24 (P5)
/250407 Design/250407 Sheet 1/CASS_PWR: CN3.C,3, FB2.1
/250407 Design/250407 Sheet 1/CASS_RD: CN3.D,4, CN4.1, RP3.4, U1.24 (~FLAG)
/250407 Design/250407 Sheet 1/CASS_SENSE: CN3.F,6, R1.2, U7.25 (P4)
/250407 Design/250407 Sheet 1/CASS_WRT: FB1.2, U7.26 (P3)
/250407 Design/250407 Sheet 1/CASS_WRT': CN3.E,5, FB1.1
/250407 Design/250407 Sheet 1/CLK: CN4.4, FB9.1
/250407 Design/250407 Sheet 1/CLK': CR102.2 (A), CR103.1 (K), FB9.2, R30.1, U2.8 (PA6), U8.10
/250407 Design/250407 Sheet 1/CLK_OUT: U2.6 (PA4), U8.11
/250407 Design/250407 Sheet 1/CNT1: CN2.4, RP3.5, U1.40 (CNT)
/250407 Design/250407 Sheet 1/CNT2: CN2.6, RP3.7, U2.40 (CNT)
/250407 Design/250407 Sheet 1/COL0: CN1.13, CN8.1, U1.2 (PA0)
/250407 Design/250407 Sheet 1/COL1: CN1.19, CN8.2, U1.3 (PA1)
/250407 Design/250407 Sheet 1/COL2: CN1.18, CN8.3, U1.4 (PA2)
/250407 Design/250407 Sheet 1/COL3: CN1.17, CN8.4, U1.5 (PA3)
/250407 Design/250407 Sheet 1/COL5: CN1.15, U1.7 (PA5)
/250407 Design/250407 Sheet 1/COL6: CN1.14, U1.8 (PA6), U28.6 (E2), U28.12 (E3)
/250407 Design/250407 Sheet 1/COL7: CN1.20, U1.9 (PA7), U28.5 (E1), U28.13 (E0)
/250407 Design/250407 Sheet 1/DATA: CN4.5, FB8.1
/250407 Design/250407 Sheet 1/DATA': CR100.2 (A), CR101.1 (K), FB8.2, R29.1, U2.9 (PA7), U8.2
/250407 Design/250407 Sheet 1/DATA_OUT: U2.7 (PA5), U8.1
/250407 Design/250407 Sheet 1/F_DIV: U29.11 (CK), U30.6 (Qc)
/250407 Design/250407 Sheet 1/GND_LED: CN10.2, FB20.2
/250407 Design/250407 Sheet 1/JOYA0: CN1.12, CN9.1, U1.10 (PB0)
/250407 Design/250407 Sheet 1/JOYA1: CN1.11, CN9.2, U1.11 (PB1)
/250407 Design/250407 Sheet 1/JOYA2: CN1.10, CN9.3, U1.12 (PB2)
/250407 Design/250407 Sheet 1/JOYA3: CN1.5, CN9.4, U1.13 (PB3)
/250407 Design/250407 Sheet 1/LED+: CN10.1, CN10.3, FB21.2
/250407 Design/250407 Sheet 1/PA2: CN2.M, U2.4 (PA2)
/250407 Design/250407 Sheet 1/PB0: CN2.C, U2.10 (PB0)
/250407 Design/250407 Sheet 1/PB1: CN2.D, U2.11 (PB1)
/250407 Design/250407 Sheet 1/PB2: CN2.E, U2.12 (PB2)
/250407 Design/250407 Sheet 1/PB3: CN2.F, U2.13 (PB3)
/250407 Design/250407 Sheet 1/PB4: CN2.H, U2.14 (PB4)
/250407 Design/250407 Sheet 1/PB5: CN2.J, U2.15 (PB5)
/250407 Design/250407 Sheet 1/PB6: CN2.K, U2.16 (PB6)
/250407 Design/250407 Sheet 1/PB7: CN2.L, U2.17 (PB7)
/250407 Design/250407 Sheet 1/PH2_FB: FB5.2, U7.39 (PHI2)
/250407 Design/250407 Sheet 1/POTAX: CN9.9, U28.8 (Y2)
/250407 Design/250407 Sheet 1/POTAY: CN9.5, U28.11 (Y3)
/250407 Design/250407 Sheet 1/POTBX: CN8.9, U28.1 (Y0)
/250407 Design/250407 Sheet 1/POTBY: CN8.5, U28.4 (Y1)
/250407 Design/250407 Sheet 1/ROW5: CN1.7, U1.15 (PB5)
/250407 Design/250407 Sheet 1/ROW6: CN1.6, U1.16 (PB6)
/250407 Design/250407 Sheet 1/ROW7: CN1.9, U1.17 (PB7)
/250407 Design/250407 Sheet 1/SP1: CN2.5, RP3.6, U1.39 (SP)
/250407 Design/250407 Sheet 1/SP2: CN2.7, RP3.8, U2.39 (SP)
/250407 Design/250407 Sheet 1/TRIGA: C38.1, R35.2, U20.6 (TRIGA)
/250407 Design/250407 Sheet 1/jumper_select: E2.2, E3.2, U29.4, U30.1 (B), U30.10 (C)
/250407 Design/250407 Sheet 1/~FLAG2: CN2.B, RP3.2, U2.24 (~FLAG)
/250407 Design/250407 Sheet 1/~PC2: CN2.8, U2.18 (~PC)
/250407 Design/250407 Sheet 1/~RESTORE: C38.2, CN1.3, R41.2
/250407 Design/250407 Sheet 2/AEC: U8.3, U14.15 (~OE), U16.5 (E1), U16.6 (E2), U16.12 (E3), U16.13 (E0), U19.16 (AEC), U26.1, U27.4, U27.12
/250407 Design/250407 Sheet 2/AUDIO_IN: C12.2, CN5.5
/250407 Design/250407 Sheet 2/AUDIO_OUT: C13.2, CN5.3
/250407 Design/250407 Sheet 2/BA: CN6.12, U17.26 (I9), U19.12 (BA), U27.9
/250407 Design/250407 Sheet 2/GR\~W: U6.10 (~WE), U17.13 (F4)
/250407 Design/250407 Sheet 2/MA0: RP2.4, U9.5 (A0), U10.5 (A0), U11.5 (A0), U12.5 (A0), U21.5 (A0), U22.5 (A0), U23.5 (A0), U24.5 (A0)
/250407 Design/250407 Sheet 2/MA1: RP2.8, U9.7 (A1), U10.7 (A1), U11.7 (A1), U12.7 (A1), U21.7 (A1), U22.7 (A1), U23.7 (A1), U24.7 (A1)
/250407 Design/250407 Sheet 2/MA2: RP2.6, U9.6 (A2), U10.6 (A2), U11.6 (A2), U12.6 (A2), U21.6 (A2), U22.6 (A2), U23.6 (A2), U24.6 (A2)
/250407 Design/250407 Sheet 2/MA3: RP2.2, U9.12 (A3), U10.12 (A3), U11.12 (A3), U12.12 (A3), U21.12 (A3), U22.12 (A3), U23.12 (A3), U24.12 (A3)
/250407 Design/250407 Sheet 2/MA4: RP1.4, U9.11 (A4), U10.11 (A4), U11.11 (A4), U12.11 (A4), U21.11 (A4), U22.11 (A4), U23.11 (A4), U24.11 (A4)
/250407 Design/250407 Sheet 2/MA5: RP1.6, U9.10 (A5), U10.10 (A5), U11.10 (A5), U12.10 (A5), U21.10 (A5), U22.10 (A5), U23.10 (A5), U24.10 (A5)
/250407 Design/250407 Sheet 2/MA6: RP1.2, U9.13 (A6), U10.13 (A6), U11.13 (A6), U12.13 (A6), U21.13 (A6), U22.13 (A6), U23.13 (A6), U24.13 (A6)
/250407 Design/250407 Sheet 2/MA7: RP1.8, U9.9 (A7), U10.9 (A7), U11.9 (A7), U12.9 (A7), U21.9 (A7), U22.9 (A7), U23.9 (A7), U24.9 (A7)
/250407 Design/250407 Sheet 2/VA0: RP2.3, U19.24 (A0/A8), U25.12 (Y3), U26.7 (D0)
/250407 Design/250407 Sheet 2/VA1: RP2.7, U19.25 (A1/A9), U25.9 (Y2), U26.13 (D1)
/250407 Design/250407 Sheet 2/VA2: RP2.5, U19.26 (A2/A10), U25.7 (Y1), U26.8 (D2)
/250407 Design/250407 Sheet 2/VA3: RP2.1, U19.27 (A3/A11), U25.4 (Y0), U26.14 (D3)
/250407 Design/250407 Sheet 2/VA4: RP1.3, U13.12 (Y3), U17.20 (I15), U19.28 (A4/A12), U26.17 (D4)
/250407 Design/250407 Sheet 2/VA5: RP1.5, U13.7 (Y1), U17.21 (I14), U19.29 (A5/A13), U26.18 (D5)
/250407 Design/250407 Sheet 2/VA6: RP1.1, U13.4 (Y0), U14.4 (~Y0), U26.4 (D6)
/250407 Design/250407 Sheet 2/VA6': U14.13 (B2), U14.14 (A2), U19.30 (A6)
/250407 Design/250407 Sheet 2/VA7: RP1.7, U13.9 (Y2), U14.7 (~Y1), U26.3 (D7)
/250407 Design/250407 Sheet 2/VA7': U14.10 (B3), U14.11 (A3), U19.31 (A7)
/250407 Design/250407 Sheet 2/~AEC: R31.1, U8.4, U13.15 (~OE), U17.25 (I10), U25.15 (~OE)
/250407 Design/250407 Sheet 2/~BASIC: U3.20 (~CS), U17.17 (F1)
/250407 Design/250407 Sheet 2/~CASRAM: R42.2, U17.18 (F0)
/250407 Design/250407 Sheet 2/~CASRAM': C204.2, R42.1, U9.15 (~CAS), U10.15 (~CAS), U11.15 (~CAS), U12.15 (~CAS), U21.15 (~CAS), U22.15 (~CAS), U23.15 (~CAS), U24.15 (~CAS)
/250407 Design/250407 Sheet 2/~CAS: C203.2, U13.1 (~SELA), U14.1 (~SELA), U17.9 (I0), U19.19 (~CAS), U25.1 (~SELA)
/250407 Design/250407 Sheet 2/~CHAROM: U5.20 (~CS), U17.15 (F3)
/250407 Design/250407 Sheet 2/~CIAS: U15.7 (1Y3), U15.15 (EN2)
/250407 Design/250407 Sheet 2/~COLOR: U15.6 (1Y2), U27.13
/250407 Design/250407 Sheet 2/~DMA: CN6.13, RP4.10, U27.5, U27.10
/250407 Design/250407 Sheet 2/~EXROM: CN6.9, RP4.9, U17.23 (I12)
/250407 Design/250407 Sheet 2/~GAME: CN6.8, RP4.7, U17.22 (I13)
/250407 Design/250407 Sheet 2/~I\O: U15.1 (EN1), U17.12 (F5)
/250407 Design/250407 Sheet 2/~KERNAL: U4.20 (~CS), U17.16 (F2)
/250407 Design/250407 Sheet 2/~RAS: U9.4 (~RAS), U10.4 (~RAS), U11.4 (~RAS), U12.4 (~RAS), U19.18 (~RAS), U21.4 (~RAS), U22.4 (~RAS), U23.4 (~RAS), U24.4 (~RAS), U26.11
/250407 Design/250407 Sheet 2/~RESET': CN6.C, FB4.1
/250407 Design/250407 Sheet 2/~ROMH: CN6.B, U17.10 (F7)
/250407 Design/250407 Sheet 2/~ROML: CN6.11, U17.11 (F6)
/250407 Design/250407 Sheet 2/~SID: U15.5 (1Y1), U18.8 (~CS)
/250407 Design/250407 Sheet 2/~VIC: U15.4 (1Y0), U19.10 (~CS)
/250407 Design/CHROMA_OUT: CN5.6, JP503.2 (B), R511.1, RV502.3
/250407 Design/COMP_OUT: C506.2, CN5.4, R506.1, R508.1
/250407 Design/LUMA_OUT: CN5.1, JP502.2 (B), R510.1, RV501.3
/250407 Design/VIC_II_CHROMA: C505.1, FB14.2, R503.1
/250407 Design/VIC_II_LUMA: D501.1 (K), FB15.2
/HF Module Replacement/+5V_HF_M_REPL: C503.1, C504.1, Q501.3 (C), Q502.3 (C), R504.1, R512.2, U501.1 (OUT)
A0: CN6.Y, U1.38 (RS0), U2.38 (RS0), U3.8 (A0), U4.8 (A0), U5.8 (A0), U6.5 (A0), U7.7 (A0), U18.9 (A0), U25.13 (B3), U26.6 (Q0)
A1: CN6.X, U1.37 (RS1), U2.37 (RS1), U3.7 (A1), U4.7 (A1), U5.7 (A1), U6.6 (A1), U7.8 (A1), U18.10 (A1), U25.10 (B2), U26.12 (Q1)
A2: CN6.W, U1.36 (RS2), U2.36 (RS2), U3.6 (A2), U4.6 (A2), U5.6 (A2), U6.7 (A2), U7.9 (A2), U18.11 (A2), U25.6 (B1), U26.9 (Q2)
A3: CN6.V, U1.35 (RS3), U2.35 (RS3), U3.5 (A3), U4.5 (A3), U5.5 (A3), U6.4 (A3), U7.10 (A3), U18.12 (A3), U25.3 (B0), U26.15 (Q3)
A4: CN6.U, U3.4 (A4), U4.4 (A4), U5.4 (A4), U6.3 (A4), U7.11 (A4), U13.13 (B3), U18.13 (A4), U26.16 (Q4)
A5: CN6.T, U3.3 (A5), U4.3 (A5), U5.3 (A5), U6.2 (A5), U7.12 (A5), U13.6 (B1), U26.19 (Q5)
A6: CN6.S, U3.2 (A6), U4.2 (A6), U5.2 (A6), U6.1 (A6), U7.13 (A6), U13.3 (B0), U26.5 (Q6)
A7: CN6.R, U3.1 (A7), U4.1 (A7), U5.1 (A7), U6.17 (A7), U7.14 (A7), U13.10 (B2), U26.2 (Q7)
A8: CN6.P, U3.23 (A8), U4.23 (A8), U5.23 (A8), U6.16 (A8), U7.15 (A8), U15.14 (A2), U19.32 (A8), U25.14 (A3)
A9: CN6.N, U3.22 (A9), U4.22 (A9), U5.22 (A9), U6.15 (A9), U7.16 (A9), U15.13 (B2), U19.33 (A9), U25.11 (A2)
A10: CN6.M, U3.19 (A10), U4.19 (A10), U5.19 (A10), U7.17 (A10), U15.2 (A1), U19.34 (A10), U25.5 (A1)
A11: CN6.L, U3.18 (A11), U4.18 (A11), U5.18 (A11), U7.18 (A11), U15.3 (B1), U19.23 (A11), U25.2 (A0)
A12: CN6.K, RP4.8, U3.21 (A12), U4.21 (A12), U7.19 (A12), U13.14 (A3), U17.27 (I8)
A13: CN6.J, RP4.6, U7.20 (A13), U13.5 (A1), U17.2 (I7)
A14: CN6.H, RP4.5, U7.22 (A14), U13.2 (A0), U17.3 (I6)
A15: CN6.F, RP4.4, U7.23 (A15), U13.11 (A2), U17.4 (I5)
BTNA\~LP: CN1.8, CN9.6, U1.14 (PB4), U19.9 (LP)
CAEC: U7.5 (~AEC), U27.6
CAN+5V: C65.1, C66.1, C102.1, C103.1, FB22.2, L2.1, VR2.2
D0: CN6.21, U1.33 (D0), U2.33 (D0), U3.9 (D0), U4.9 (D0), U5.9 (D0), U7.37 (D0), U16.11 (Y3), U18.15 (D0), U19.7 (D0), U21.2 (D1), U21.14 (D0)
D1: CN6.20, U1.32 (D1), U2.32 (D1), U3.10 (D1), U4.10 (D1), U5.10 (D1), U7.36 (D1), U9.2 (D1), U9.14 (D0), U16.8 (Y2), U18.16 (D1), U19.6 (D1)
D2: CN6.19, U1.31 (D2), U2.31 (D2), U3.11 (D2), U4.11 (D2), U5.11 (D2), U7.35 (D2), U16.4 (Y1), U18.17 (D2), U19.5 (D2), U22.2 (D1), U22.14 (D0)
D3: CN6.18, U1.30 (D3), U2.30 (D3), U3.13 (D3), U4.13 (D3), U5.13 (D3), U7.34 (D3), U10.2 (D1), U10.14 (D0), U16.1 (Y0), U18.18 (D3), U19.4 (D3)
D4: CN6.17, U1.29 (D4), U2.29 (D4), U3.14 (D4), U4.14 (D4), U5.14 (D4), U7.33 (D4), U18.19 (D4), U19.3 (D4), U23.2 (D1), U23.14 (D0)
D5: CN6.16, U1.28 (D5), U2.28 (D5), U3.15 (D5), U4.15 (D5), U5.15 (D5), U7.32 (D5), U11.2 (D1), U11.14 (D0), U18.20 (D5), U19.2 (D5)
D6: CN6.15, U1.27 (D6), U2.27 (D6), U3.16 (D6), U4.16 (D6), U5.16 (D6), U7.31 (D6), U18.21 (D6), U19.1 (D6), U24.2 (D1), U24.14 (D0)
D7: CN6.14, U1.26 (D7), U2.26 (D7), U3.17 (D7), U4.17 (D7), U5.17 (D7), U7.30 (D7), U12.2 (D1), U12.14 (D0), U18.22 (D7), U19.39 (D7)
DOT_CLOCK: C36.1, CN6.6, FB17.2, U19.22 (PHI_IN)
Earth: C1.2, C2.2, C3.1, C4.1, C5.1, C6.1, C7.2, C8.2, C9.2, C14.2, C17.2, C19.2, C22.2, C23.2, C24.2, C25.2, C26.2, C27.2, C28.2, C29.1, C30.2, C31.1, C32.1, C33.2, C34.2, C36.2, C37.2, C39.1, C40.2, C41.2, C42.2, C43.2, C44.1, C45.2, C46.2, C47.2, C48.2, C49.2, C50.2, C51.2, C52.2, C53.2, C54.2, C56.2, C57.2, C59.2, C60.2, C62.2, C65.2, C66.2, C67.2, C68.2, C74.2, C82.2, C83.2, C84.2, C88.2, C89.2, C91.2, C92.2, C93.2, C94.2, C95.2, C96.1, C97.1, C98.2, C99.1, C100.1, C101.2, C102.2, C103.2, C105.1, C107.2, C108.2, C200.2, C203.1, C204.1, C205.2, C501.2, C502.2, C503.2, C504.2, CN1.1, CN2.1, CN2.12, CN2.A, CN2.N, CN3.A,1, CN4.2, CN5.2, CN6.1, CN6.22, CN6.A, CN6.Z, CN7.1, CN7.2, CN7.3, CN8.8, CN9.8, CR1.2 (A), CR2.2 (A), CR4.3, CR101.2 (A), CR103.2 (A), E3.1, FB20.1, Q2.1 (E), R3.2, R6.1, R38.1, R52.2, R503.2, R505.2, R508.2, R510.2, R511.2, U1.1 (GND), U2.1 (GND), U3.12 (GND), U4.12 (GND), U5.12 (GND), U6.9 (GND), U7.21 (GND), U8.7, U9.16 (GND), U10.16 (GND), U11.16 (GND), U12.16 (GND), U13.8, U14.8 (GND), U15.8, U16.7 (VSS), U17.14 (GND), U17.19 (~OE), U18.14 (GND), U19.20 (GND), U20.7 (GND), U21.16 (GND), U22.16 (GND), U23.16 (GND), U24.16 (GND), U25.8, U26.10, U27.7, U28.7 (VSS), U29.1, U29.2 (D), U29.3 (CK), U29.7, U30.8 (GND), U30.14 (CLR), U31.3, U31.6 (~EN), U31.8 (GND), U31.9, U31.11 (~EN), U31.14 (RNG), U32.7, U501.2 (GND), VR1.3, VR2.3, Y1.3
unnamed: C20.1, CN7.7, L4.2
unnamed: C21.1, C98.1, F1.2, L4.1
unnamed: C70.1, Y1.2
unnamed: C70.2, U31.13
unnamed: C85.1, R17.2
unnamed: C97.2, L5.2, SW1.4
unnamed: C107.1, R26.2, U31.15
unnamed: CN7.4, CN7.5, SW1.5
unnamed: CN7.6, SW1.2
unnamed: C200.1, CR1.1 (K), R5.2, R100.1
unnamed: C18.2, CR2.1 (K), Q1.3 (B), Q2.2 (C), R2.2
unnamed: C90.1, CR5.2 (A), CR6.1 (K)
unnamed: C88.1, C89.1, CR5.1 (K), VR1.1
unnamed: D501.2 (A), Q501.1 (B), R512.1
unnamed: FB13.2, R7.2
unnamed: FB19.1, L2.2
unnamed: FB21.1, R39.2
unnamed: JP502.1 (A), R507.1, RV501.2
unnamed: JP503.1 (A), R509.1, RV502.2
unnamed: L501.2, R506.2
unnamed: Q1.1 (E), Q3.1 (B)
unnamed: Q2.3 (B), R3.1, R4.1
unnamed: FB2.2, Q3.3 (E)
unnamed: C85.2, Q7.3 (B), R19.1
unnamed: Q7.1 (E), U32.9
unnamed: C37.1, Q8.3 (B), R7.1
unnamed: C13.1, C205.1, Q8.1 (E), R38.2
unnamed: L501.1, Q501.2 (E), R507.2
unnamed: C505.2, Q502.1 (B), R504.2, R505.1
unnamed: C506.1, Q502.2 (E), R509.2
unnamed: R19.2, U32.5, U32.10
unnamed: R27.1, R53.2
unnamed: R27.2, R52.1
unnamed: R37.1, R100.2, U27.2
unnamed: U6.8 (~CS), U27.11
unnamed: U14.3 (B0), U14.12 (~Y2)
unnamed: U14.6 (B1), U14.9 (~Y3)
unnamed: CN6.7, U15.10 (2Y2)
unnamed: CN6.10, U15.9 (2Y3)
unnamed: U6.11 (D3), U16.2 (Z0), U19.35 (D11)
unnamed: U6.12 (D2), U16.3 (Z1), U19.36 (D10)
unnamed: U6.13 (D1), U16.9 (Z2), U19.37 (D9)
unnamed: U6.14 (D0), U16.10 (Z3), U19.38 (D8)
unnamed: FB13.1, R6.2, U18.27 (AUDIO)
unnamed: C10.1, U18.1 (CAP1A)
unnamed: C10.2, U18.2 (CAP1B)
unnamed: C11.1, U18.3 (CAP2A)
unnamed: C11.2, U18.4 (CAP2B)
unnamed: C12.1, U18.26 (EXT_IN)
unnamed: C50.1, FB10.1, U18.25 (VCC)
unnamed: C51.1, FB11.1, U18.28 (VDD)
unnamed: FB14.1, U19.14 (CHROMA)
unnamed: FB23.1, U19.17 (PHI0_OUT)
unnamed: FB15.1, U19.15 (SYNC_LUMA)
unnamed: C60.1, C101.1, FB22.1, U19.40 (VCC)
unnamed: C54.1, FB12.1, U19.13 (VDD)
unnamed: C23.1, R33.2, U20.1 (DISA), U20.2 (THRA)
unnamed: U8.5, U20.5 (OUTA)
unnamed: C24.1, R34.2, U20.12 (THRB), U20.13 (DISB)
unnamed: U8.9, U20.9 (OUTB)
unnamed: C105.2, R50.2, U20.8 (TRIGB)
unnamed: U29.5 (Q), U30.9 (D)
unnamed: U29.8 (~Q), U29.12 (D)
unnamed: U29.9 (Q), U32.1
unnamed: C83.1, U30.11 (LOAD), U30.12 (CRY)
unnamed: U31.12, Y1.1
unnamed: C86.2, U31.4 (CX1)
unnamed: C86.1, U31.5 (CX2)
unnamed: R16.2, R17.1, U31.2 (FC), U32.8
unnamed: FB17.1, U31.7 (Y)
unnamed: C108.1, R27.3, U31.1 (FC)
unnamed: FB16.1, U31.10 (Y)
unnamed: U32.2, U32.11
unnamed: U32.4, U32.13
unnamed: C501.1, C502.1, R501.1, U501.3 (IN)
PHI0: FB23.2, U7.1 (PH0IN), U32.3
PHI2: CN6.E, FB5.1, U1.25 (PH2), U2.25 (PH2), U18.6 (PHI2)
PHI_COLOR: FB16.2, U19.21 (PHI_COLOR), U30.5 (CNT_UP)
POTX: C48.1, U18.24 (POTX), U28.2 (Z0), U28.9 (Z2)
POTY: C93.1, U18.23 (POTY), U28.3 (Z1), U28.10 (Z3)
RDY: U7.2 (RDY), U27.8
R\~W: CN6.5, R51.1, U1.22 (R/~W), U2.22 (R/~W), U7.38 (R/~W), U9.3 (~WE), U10.3 (~WE), U11.3 (~WE), U12.3 (~WE), U17.24 (I11), U18.7 (R/~W), U19.11 (R/~W), U21.3 (~WE), U22.3 (~WE), U23.3 (~WE), U24.3 (~WE)
~CHAREN: R43.2, U7.27 (P2), U17.6 (I3)
~CIA1: U1.23 (~CS), U15.12 (2Y0)
~CIA2: U2.23 (~CS), U15.11 (2Y1)
~HIRAM: R44.2, U7.28 (P1), U17.7 (I2)
~IRQ: CN6.4, RP4.3, U1.21 (~IRQ), U7.3 (~IRQ), U19.8 (~IRQ)
~LORAM: R45.2, U7.29 (P0), U17.8 (I1)
~NMI: CN6.D, RP3.3, U2.21 (~IRQ), U7.4 (~NMI), U8.6
~RESET: CN2.3, CN4.6, FB4.2, R36.2, U1.34 (~RES), U2.34 (~RES), U7.40 (~RES), U8.8, U18.5 (~RES)
~VA14: U2.2 (PA0), U14.2 (A0), U17.5 (I4)
~VA15: U2.3 (PA1), U14.5 (A1)

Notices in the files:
hardware/main-board/README.md:
Copyright Bwack 2025.
Modifications copyright (c) 2026 Mariella de Jong and contributors.
The original design is licensed under the
[CERN Open Hardware Licence v1.2](../../LICENSES/CERN-OHL-1.2.txt). The
modified design is licensed under the
as permitted by section 3.4(e) of CERN-OHL v1.2.
Source Location:
The HF module replacement circuit, on the sheet `vic_ii_hf_av_out.kicad_sch`
(formerly `hf_module_replacement.kicad_sch`), is derived from the
Copyright (c) 2020 mbarszcz-pcb, licensed under the
Licence | MIT License
